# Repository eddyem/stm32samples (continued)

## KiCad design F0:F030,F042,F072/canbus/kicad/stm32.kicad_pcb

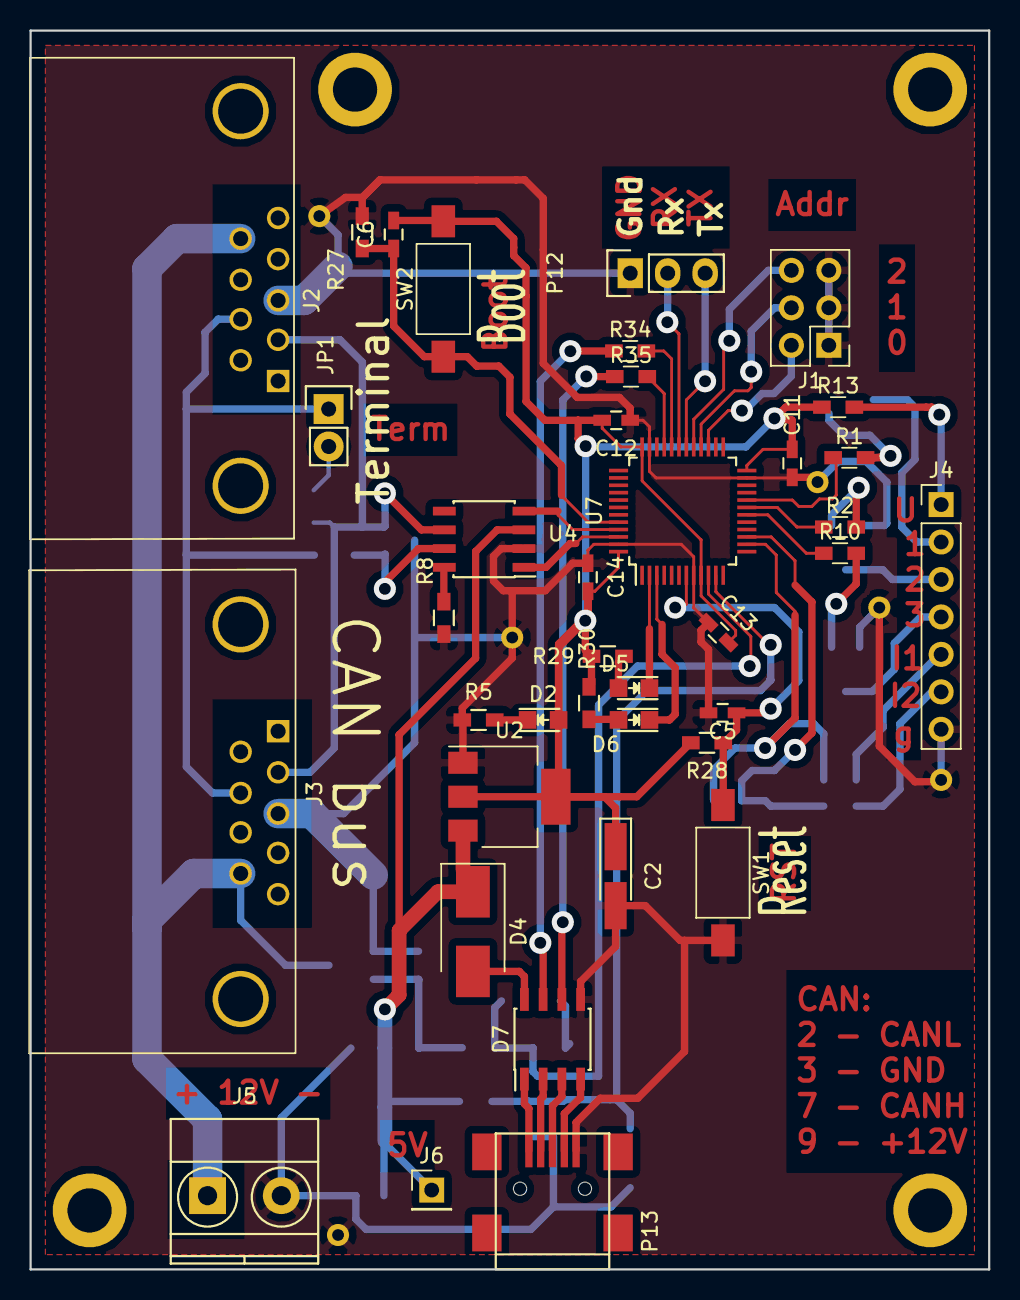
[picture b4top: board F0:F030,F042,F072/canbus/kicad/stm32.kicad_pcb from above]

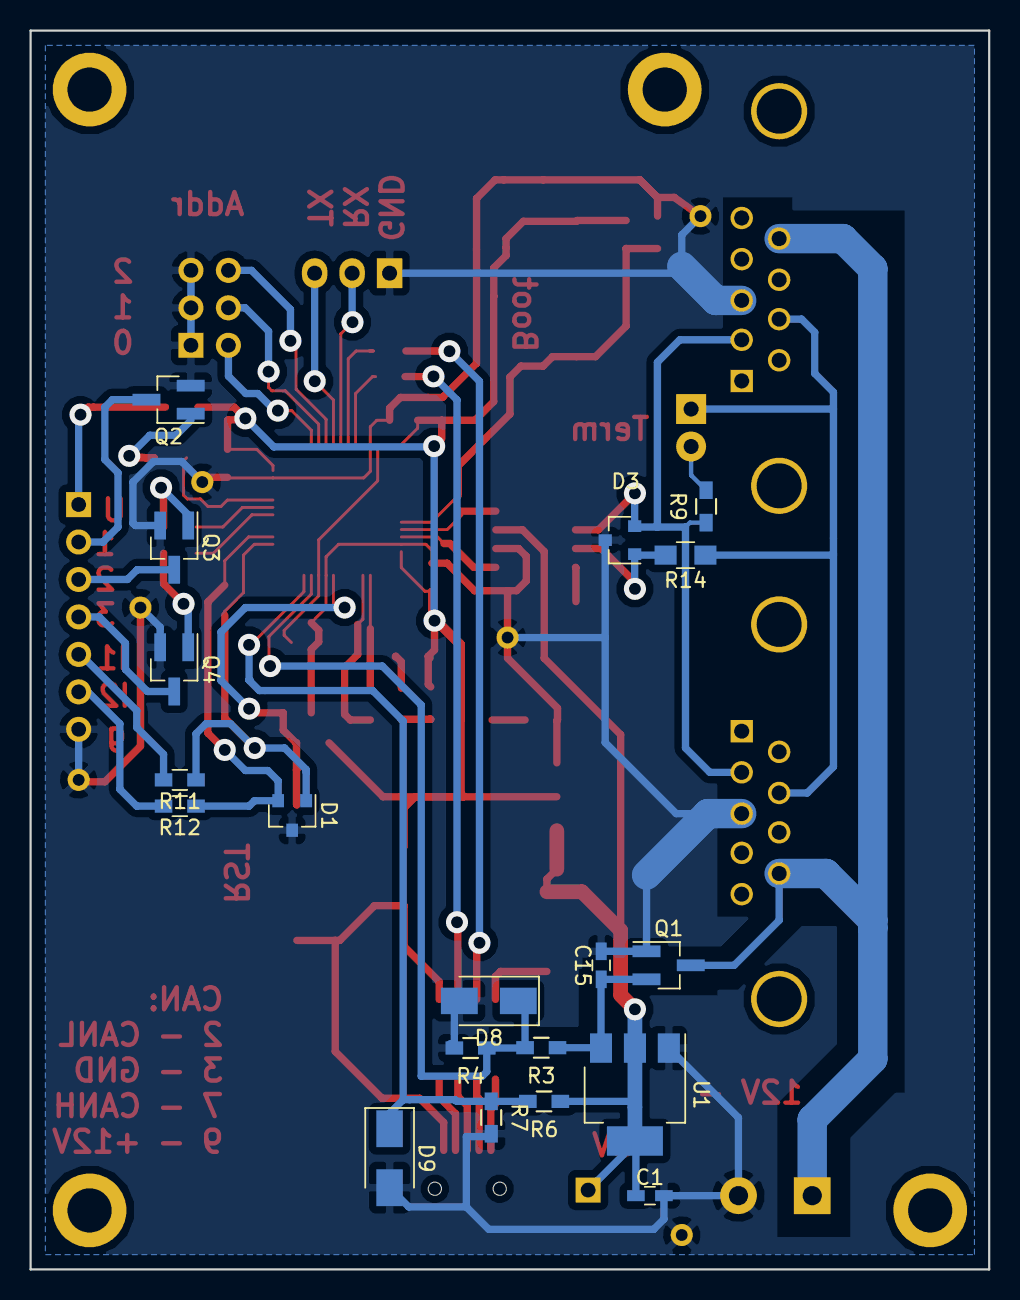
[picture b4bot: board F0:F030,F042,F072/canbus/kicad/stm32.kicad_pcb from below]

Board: 2 copper layers, 65.0 x 84.0 mm, 61 parts (19 on the bottom side), 49 nets.

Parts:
C1, C5, C6, C11, C12, C13, C14, C15: 0.1; C_0603_HandSoldering
C2: 47u; Tantalum_Case-A_EIA-3216-18_Hand
D1: SP0502BAHT; SOT-23
D2: LED; LED_0805
D3: PESD1CAN; SOT-23
D4: MBRS130L; D_SMB_Handsoldering
D5: LED0; LED_0805
D6: LED1; LED_0805
D7: USB6B1; SOIC-8_3.9x4.9mm_Pitch1.27mm
D8, D9: SMAJ5.0A; D_SMA
J1: CONN_02X03; Pin_Header_Straight_2x03_Pitch2.54mm
J2: DB9_Female; DB9FC
J3: DB9_Male; DB9MC
J4: Conn_01x07; Pin_Header_Straight_1x07_Pitch2.54mm
J5: 12v; TerminalBlock_Pheonix_MKDS1.5-2pol
J6: Conn_01x01; Pin_Header_Straight_1x01_Pitch2.54mm
JP1: Terminal; Pin_Header_Straight_1x02
P12: USART_BOOT; Pin_Header_Straight_1x03
P13: USB_A; USB_Mini-B
P15, P16, P17, P18: Hole; Hole_3mm
Q1: AO3407; SOT-23_Handsoldering
Q2, Q3, Q4: SI2300; SOT-23_Handsoldering
R1, R2, R5, R10, R11, R12, R29, R30: 330; R_0603_HandSoldering
R3: 220k; R_0603_HandSoldering
R4: 56k; R_0603_HandSoldering
R6, R7: 47k; R_0603_HandSoldering
R8: 4k7; R_0603_HandSoldering
R9: 120; R_0603_HandSoldering
R13: 4.7; R_0603_HandSoldering
R14: 0; R_0805_HandSoldering
R27, R28: 10k; R_0603_HandSoldering
R34, R35: 22; R_0603_HandSoldering
SW1: Reset; SW_SPST_FSMSM
SW2: Boot; SW_SPST_FSMSM
U1: LM1117-5.0; SOT-223
U2: LM1117-3.3; SOT-223
U4: MCP2551-I/SN; SOIC-8_3.9x4.9mm_Pitch1.27mm
U7: STM32F042C6Tx; LQFP-48_7x7mm_Pitch0.5mm

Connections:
+3V3: C2.1, C6.2, C11.2, C12.2, C13.2, C14.2, D2.2, R13.1, R28.2, R29.2, R30.2, SW2.2, U2.2, U2.4, U7.9, U7.24, U7.36, U7.48
+5V: C1.1, D4.1, J6.1, R6.1, U1.2, U1.4, U2.3, U4.3
/5Vusb: D4.2, D7.8
/12Vin: C15.1, Q1.2, R3.1, U1.3
/BOOT0: C6.1, R27.1, SW2.1, U7.44
/CAN_Rx: U4.4, U7.45
/CAN_Tx: U4.1, U7.46
/INP1: D1.1, R11.1, U7.14
/INP2: D1.2, R12.1, U7.15
/LED0: D5.1, U7.2
/LED1: D6.1, U7.3
/NRST: C5.1, R28.1, SW1.1, U7.7
/O1: R1.1, U7.20
/O2: R2.1, U7.19
/O3: R10.1, U7.18
/OUTP1: J4.2, Q2.3
/OUTP2: J4.3, Q3.3
/OUTP3: J4.4, Q4.3
/Rx: P12.2, U7.31
/Tx: P12.3, U7.30
/V5: D9.1, R6.2, R7.1, U7.11
/V12: D8.1, R3.2, R4.1, U7.10
/brdaddr0: J1.2, U7.27
/brdaddr1: J1.4, U7.28
/brdaddr2: J1.6, U7.29
GND: C1.2, C2.2, C5.2, C11.1, C12.1, C13.1, C14.1, C15.2, D1.3, D3.3, D7.5, D8.2, D9.2, J1.1, J1.3, J1.5, J2.3, J3.3, J4.7, J5.2, P12.1, P13.5, Q1.1, Q2.2, Q3.2, Q4.2, R4.2, R5.1, R7.2, R8.2, R27.2, SW1.2, U1.1, U2.1, U4.2, U7.8, U7.23, U7.35, U7.47
unnamed: D2.1, R5.2
unnamed: D3.1, R14.2, U4.7
unnamed: D3.2, J2.2, J3.2, R9.1, U4.6
unnamed: D5.2, R29.1
unnamed: D6.2, R30.1
unnamed: D7.1, P13.1
unnamed: D7.2, P13.2
unnamed: D7.3, P13.3
unnamed: D7.4, P13.4
unnamed: D7.6, R35.1
unnamed: D7.7, R34.1
unnamed: J2.7, J3.7, JP1.1, R14.1
unnamed: J2.9, J3.9, J5.1, Q1.3
unnamed: J4.1, R13.2
unnamed: J4.5, R11.2
unnamed: J4.6, R12.2
unnamed: JP1.2, R9.2
unnamed: Q2.1, R1.2
unnamed: Q3.1, R2.2
unnamed: Q4.1, R10.2
unnamed: R8.1, U4.8
unnamed: R34.2, U7.32
unnamed: R35.2, U7.33

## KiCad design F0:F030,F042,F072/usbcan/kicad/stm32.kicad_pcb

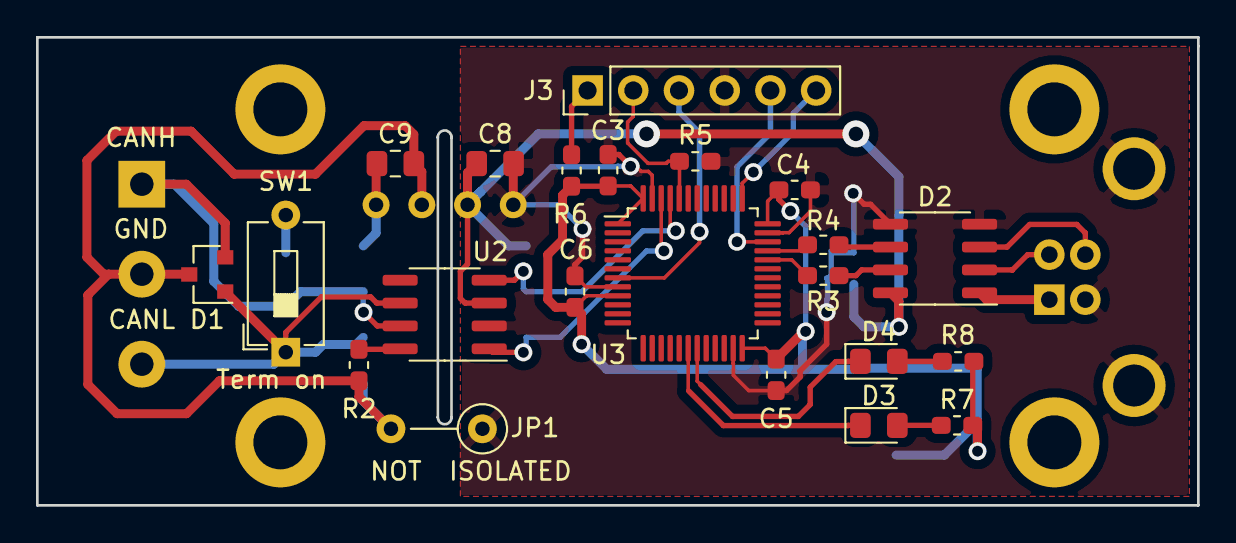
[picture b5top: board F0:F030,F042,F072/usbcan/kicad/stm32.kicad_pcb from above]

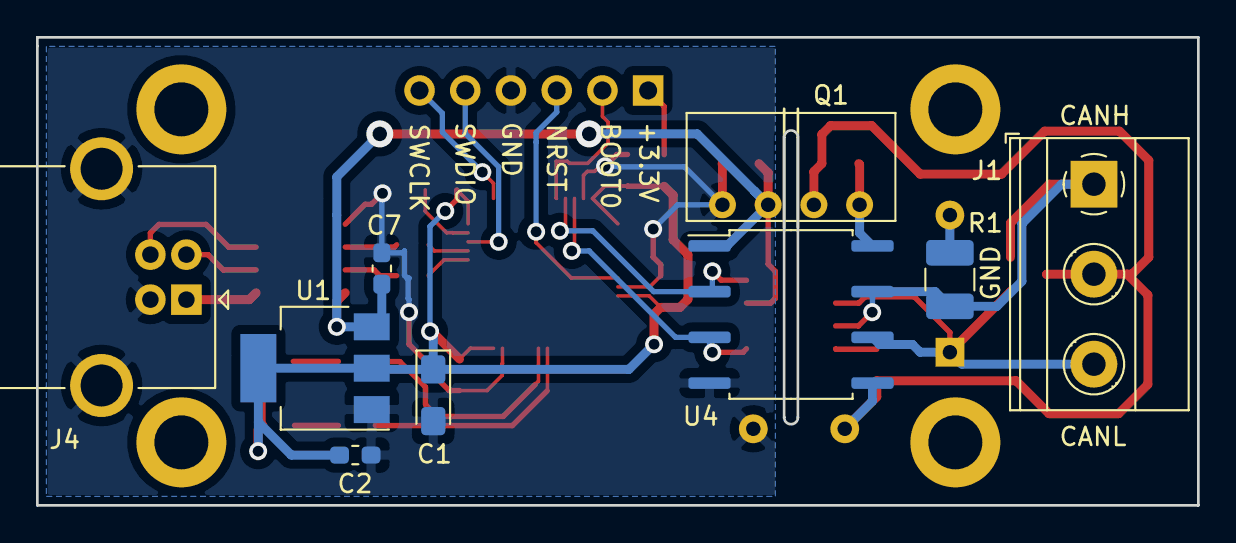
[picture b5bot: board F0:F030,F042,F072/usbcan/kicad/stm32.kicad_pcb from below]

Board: 2 copper layers, 64.5 x 26.0 mm, 35 parts (9 on the bottom side), 27 nets.

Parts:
C1: 47u; CP_EIA-3216-18_Kemet-A_Pad1.58x1.35mm_HandSolder
C2, C3, C4, C5, C6, C7: 0.1; C_0603_1608Metric_Pad1.05x0.95mm_HandSolder
C8, C9: 1; C_0805_2012Metric_Pad1.15x1.40mm_HandSolder
D1: PESD1CAN; SOT-23
D2: USB6B1; SOIC-8_3.9x4.9mm_P1.27mm
D3: LED0; LED_0805_2012Metric_Pad1.15x1.40mm_HandSolder
D4: LED1; LED_0805_2012Metric_Pad1.15x1.40mm_HandSolder
J1: Screw_Terminal_01x03; TerminalBlock_Phoenix_MKDS-1,5-3_1x03_P5.00mm_Horizontal
J3: SWDetc; PinHeader_1x06_P2.54mm_Vertical
J4: USB_B; USB_B_OST_USB-B1HSxx_Horizontal
JP1: NON-ISOL; R_Axial_DIN0207_L6.3mm_D2.5mm_P5.08mm_Vertical
P1, P2, P3, P4: Hole; Hole_3mm
Q1: B0505S; B0x0xS
R1: 120; R_1210_3225Metric_Pad1.42x2.65mm_HandSolder
R2: 4k7; R_0603_1608Metric_Pad1.05x0.95mm_HandSolder
R3, R4, R6: 22; R_0603_1608Metric_Pad1.05x0.95mm_HandSolder
R5: 10k; R_0603_1608Metric_Pad1.05x0.95mm_HandSolder
R7, R8: 330; R_0603_1608Metric_Pad1.05x0.95mm_HandSolder
SW1: SW_DIP_x01; SW_DIP_SPSTx01_Slide_6.7x4.1mm_W7.62mm_P2.54mm_LowProfile
U1: LM1117-3.3; SOT-223-3_TabPin2
U2: MCP2551-I/SN; SOIC-8_3.9x4.9mm_P1.27mm
U3: STM32F072C8Tx; LQFP-48_7x7mm_P0.5mm
U4: ISO1050DUB; SOP-8_6.62x9.15mm_P2.54mm

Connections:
+3V3: C1.1, C2.1, C3.2, C4.2, C5.2, C6.2, R6.1, R7.2, R8.2, U1.2, U3.1, U3.9, U3.24, U3.36, U3.48
+5V: C7.1, C8.1, D2.8, Q1.2, U1.3, U2.3, U4.1
/BOOT0: J3.2, R5.2, U3.44
/CANH: D1.2, J1.1, R1.2, U2.7, U4.7
/CANL: D1.1, J1.3, SW1.1, U2.6, U4.6
/CAN_Rx: U2.4, U3.45, U4.2
/CAN_Tx: U2.1, U3.46, U4.3
/LED0: D3.1, U3.18
/LED1: D4.1, U3.19
/NRST: J3.3, U3.7
/SWCLK: J3.6, U3.37
/SWDIO: J3.5, U3.34
Earth: C9.2, D1.3, J1.2, JP1.2, Q1.3, R2.2, U4.5
GND: C1.2, C2.2, C3.1, C4.1, C5.1, C6.1, C7.2, C8.2, D2.4, D2.5, J3.4, J4.4, J4.5, JP1.1, Q1.1, R5.1, U1.1, U2.2, U3.8, U3.23, U3.35, U3.47, U4.4
unnamed: C9.1, Q1.4, U4.8
unnamed: D2.1, J4.1
unnamed: D2.2, J4.2
unnamed: D2.3, J4.3
unnamed: D2.6, R4.1
unnamed: D2.7, R3.1
unnamed: D3.2, R7.1
unnamed: D4.2, R8.1
unnamed: J3.1, R6.2
unnamed: R1.1, SW1.2
unnamed: R2.1, U2.8
unnamed: R3.2, U3.32
unnamed: R4.2, U3.33

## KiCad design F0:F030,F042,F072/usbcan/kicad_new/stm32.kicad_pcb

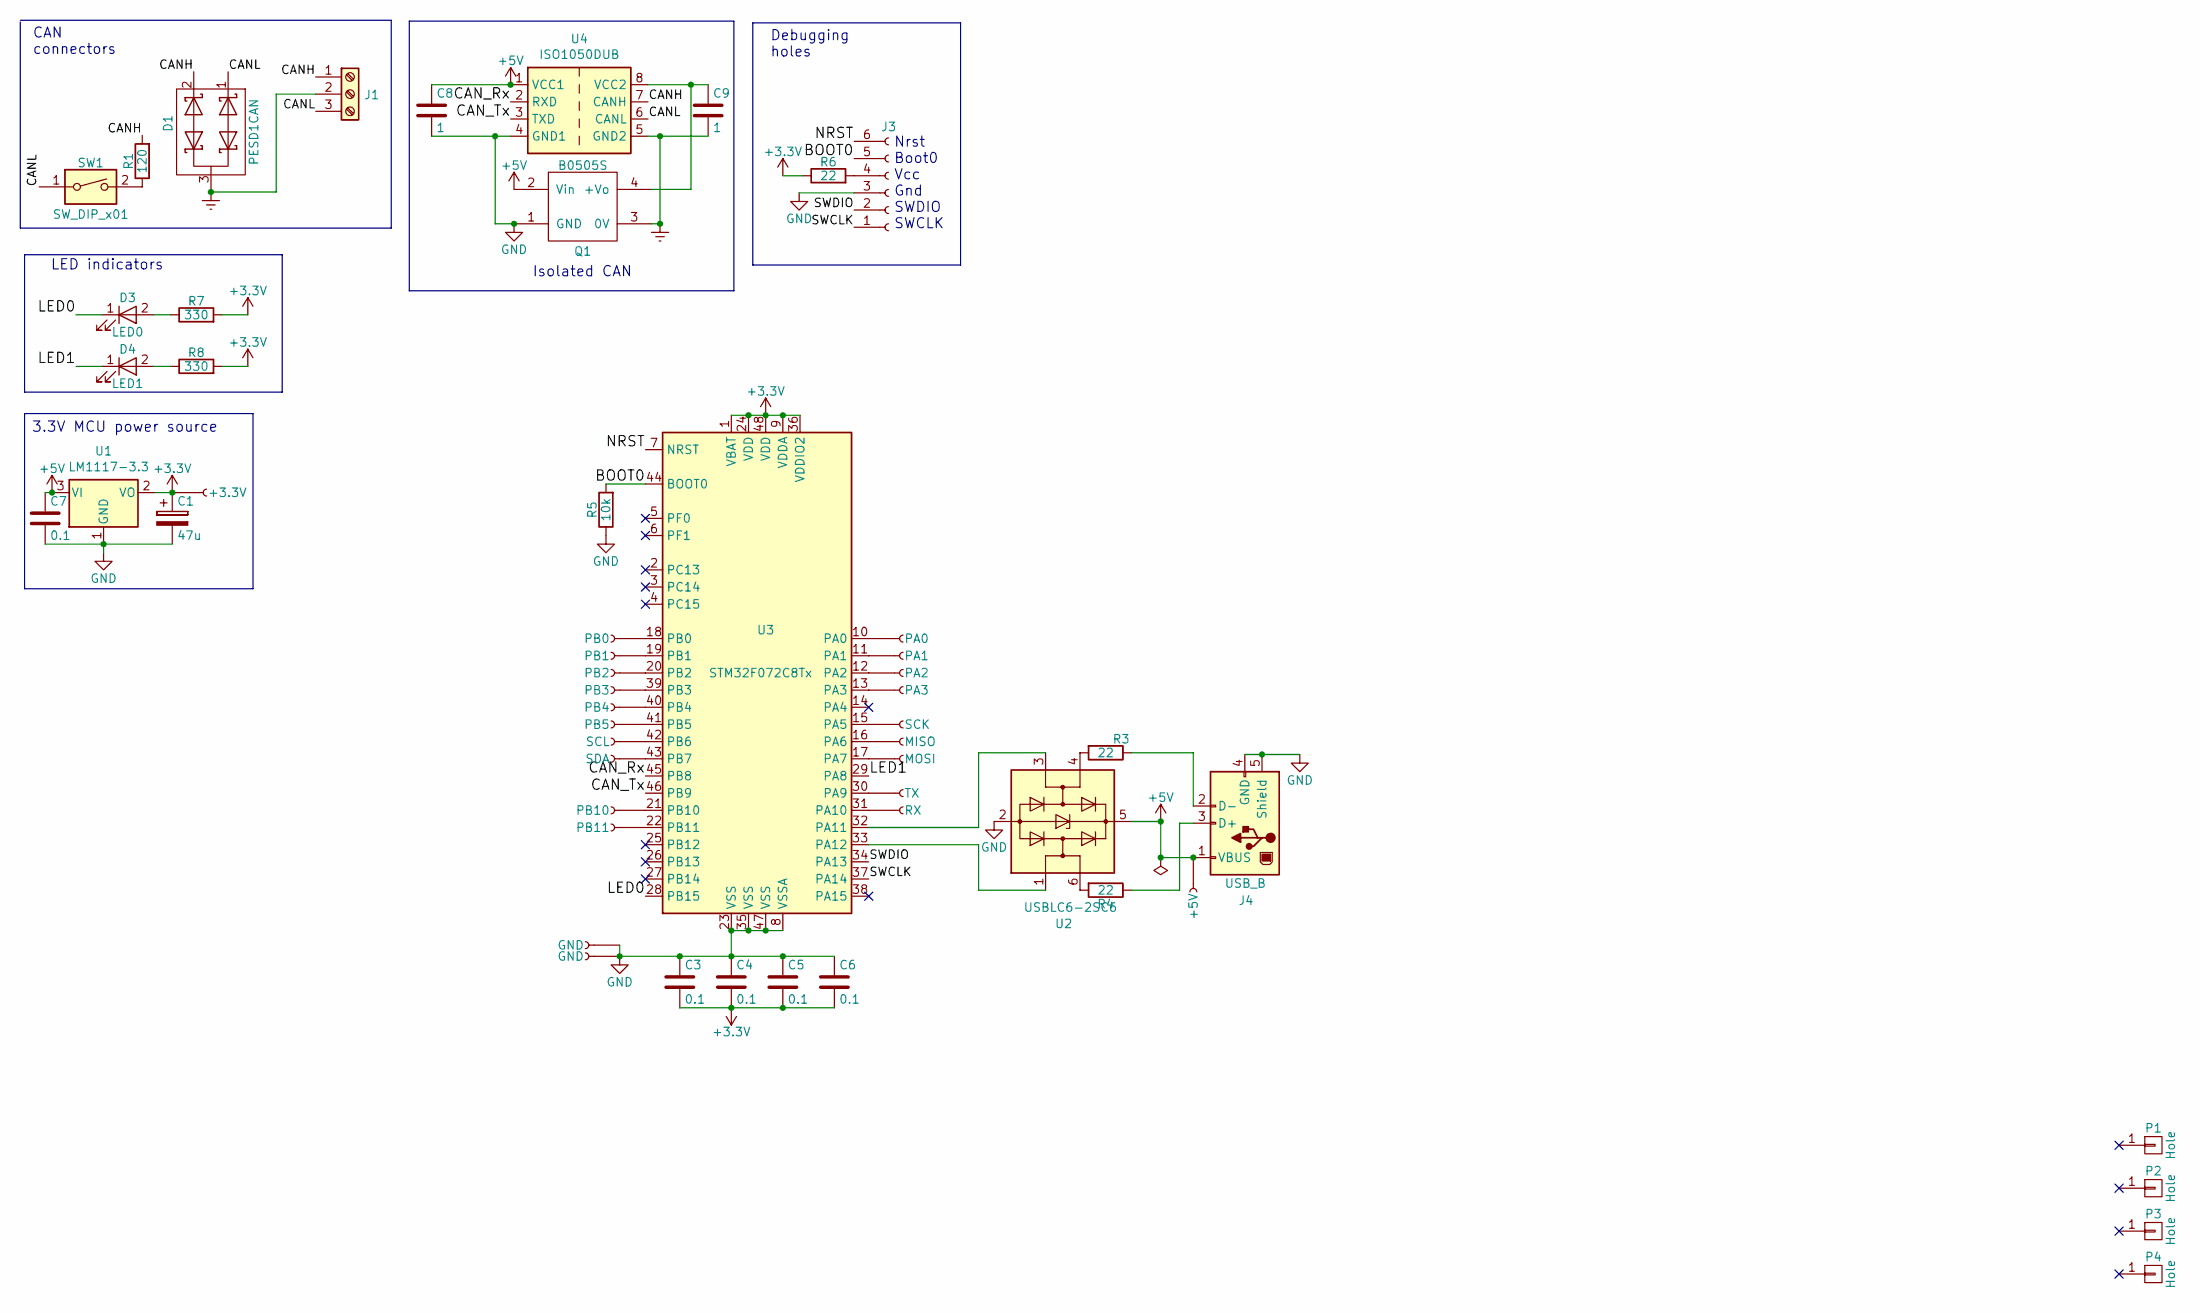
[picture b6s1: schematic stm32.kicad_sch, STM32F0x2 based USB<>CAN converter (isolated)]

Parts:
C1: 47u; CP_EIA-3216-18_Kemet-A_Pad1.58x1.35mm_HandSolder
C3, C4, C5, C6, C7: 0.1; C_0603_1608Metric_Pad1.05x0.95mm_HandSolder
C8, C9: 1; C_0805_2012Metric_Pad1.15x1.40mm_HandSolder
D1: PESD1CAN; SOT-23
D3: LED0; LED_0805_2012Metric_Pad1.15x1.40mm_HandSolder
D4: LED1; LED_0805_2012Metric_Pad1.15x1.40mm_HandSolder
J1: Screw_Terminal_01x03; TerminalBlock_Phoenix_MKDS-1,5-3_1x03_P5.00mm_Horizontal
J2: SCK; TestPoint_THTPad_1.5x1.5mm_Drill0.7mm
J3: SWDetc; PinHeader_1x06_P1.27mm_Vertical
J4: USB_B; USB_B_Lumberg_2411_02_Horizontal
J5: MISO; TestPoint_THTPad_1.5x1.5mm_Drill0.7mm
J6: MOSI; TestPoint_THTPad_1.5x1.5mm_Drill0.7mm
J7: TX; TestPoint_THTPad_1.5x1.5mm_Drill0.7mm
J8: RX; TestPoint_THTPad_1.5x1.5mm_Drill0.7mm
J9: SCL; TestPoint_THTPad_1.5x1.5mm_Drill0.7mm
J10: SDA; TestPoint_THTPad_1.5x1.5mm_Drill0.7mm
J11: PB0; TestPoint_THTPad_1.5x1.5mm_Drill0.7mm
J12: PB1; TestPoint_THTPad_1.5x1.5mm_Drill0.7mm
J13: PB4; TestPoint_THTPad_1.5x1.5mm_Drill0.7mm
J14: PB5; TestPoint_THTPad_1.5x1.5mm_Drill0.7mm
J15: PB2; TestPoint_THTPad_1.5x1.5mm_Drill0.7mm
J16: PB3; TestPoint_THTPad_1.5x1.5mm_Drill0.7mm
J17, J18: GND; TestPoint_THTPad_1.5x1.5mm_Drill0.7mm
J19: +3.3V; TestPoint_THTPad_1.5x1.5mm_Drill0.7mm
J20: +5V; TestPoint_THTPad_1.5x1.5mm_Drill0.7mm
J21: PA0; TestPoint_THTPad_1.0x1.0mm_Drill0.5mm
J22: PA1; TestPoint_THTPad_1.0x1.0mm_Drill0.5mm
J23: PA2; TestPoint_THTPad_1.0x1.0mm_Drill0.5mm
J24: PA3; TestPoint_THTPad_1.0x1.0mm_Drill0.5mm
J25: PB10; TestPoint_THTPad_1.5x1.5mm_Drill0.7mm
J26: PB11; TestPoint_THTPad_1.5x1.5mm_Drill0.7mm
P1, P2, P3, P4: Hole; Hole_3mm
Q1: B0505S; B0x0xS
R1: 120; R_1210_3225Metric_Pad1.42x2.65mm_HandSolder
R3, R4, R6: 22; R_0603_1608Metric_Pad1.05x0.95mm_HandSolder
R5: 10k; R_0603_1608Metric_Pad1.05x0.95mm_HandSolder
R7, R8: 330; R_0603_1608Metric_Pad1.05x0.95mm_HandSolder
SW1: SW_DIP_x01; SW_DIP_SPSTx01_Slide_6.7x4.1mm_W7.62mm_P2.54mm_LowProfile
U1: LM1117-3.3; SOT-223-3_TabPin2
U2: USBLC6-2SC6; SOT-23-6_Handsoldering
U3: STM32F072C8Tx; LQFP-48_7x7mm_P0.5mm
U4: ISO1050DUB; SOP-8_6.62x9.15mm_P2.54mm

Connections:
+3V3: C1.1, C3.2, C4.2, C5.2, C6.2, J19.1, R6.1, R7.2, R8.2, U1.2 (VO), U3.1 (VBAT), U3.9 (VDDA), U3.24 (VDD), U3.36 (VDDIO2), U3.48 (VDD)
+5V: C7.1, C8.1, J4.1 (VBUS), J20.1, Q1.2 (Vin), U1.3 (VI), U2.5 (VBUS), U4.1 (VCC1)
/BOOT0: J3.5, R5.2, U3.44 (BOOT0)
/CANH: D1.2 (K), J1.1, R1.2, U4.7 (CANH)
/CANL: D1.1 (K), J1.3, SW1.1, U4.6 (CANL)
/CAN_Rx: U3.45 (PB8), U4.2 (RXD)
/CAN_Tx: U3.46 (PB9), U4.3 (TXD)
/LED0: D3.1 (K), U3.28 (PB15)
/LED1: D4.1 (K), U3.29 (PA8)
/NRST: J3.6, U3.7 (NRST)
/SWCLK: J3.1, U3.37 (PA14)
/SWDIO: J3.2, U3.34 (PA13)
Earth: C9.2, D1.3 (O), J1.2, Q1.3 (0V), U4.5 (GND2)
GND: C1.2, C3.1, C4.1, C5.1, C6.1, C7.2, C8.2, J3.3, J4.4 (GND), J4.5 (Shield), J17.1, J18.1, Q1.1 (GND), R5.1, U1.1 (GND), U2.2 (GND), U3.8 (VSSA), U3.23 (VSS), U3.35 (VSS), U3.47 (VSS), U4.4 (GND1)
unnamed: C9.1, Q1.4 (+Vo), U4.8 (VCC2)
unnamed: D3.2 (A), R7.1
unnamed: D4.2 (A), R8.1
unnamed: J2.1, U3.15 (PA5)
unnamed: J3.4, R6.2
unnamed: J4.2 (D-), R3.1
unnamed: J4.3 (D+), R4.1
unnamed: J5.1, U3.16 (PA6)
unnamed: J6.1, U3.17 (PA7)
unnamed: J7.1, U3.30 (PA9)
unnamed: J8.1, U3.31 (PA10)
unnamed: J9.1, U3.42 (PB6)
unnamed: J10.1, U3.43 (PB7)
unnamed: J11.1, U3.18 (PB0)
unnamed: J12.1, U3.19 (PB1)
unnamed: J13.1, U3.40 (PB4)
unnamed: J14.1, U3.41 (PB5)
unnamed: J15.1, U3.20 (PB2)
unnamed: J16.1, U3.39 (PB3)
unnamed: J21.1, U3.10 (PA0)
unnamed: J22.1, U3.11 (PA1)
unnamed: J23.1, U3.12 (PA2)
unnamed: J24.1, U3.13 (PA3)
unnamed: J25.1, U3.21 (PB10)
unnamed: J26.1, U3.22 (PB11)
unnamed: R1.1, SW1.2
unnamed: R3.2, U2.4 (I/O2)
unnamed: R4.2, U2.6 (I/O1)
unnamed: U2.1 (I/O1), U3.33 (PA12)
unnamed: U2.3 (I/O2), U3.32 (PA11)

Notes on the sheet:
LED indicators
Isolated CAN
Debugging holes
3.3V MCU power source
Nrst Boot0 Vcc Gnd SWDIO SWCLK
CAN connectors

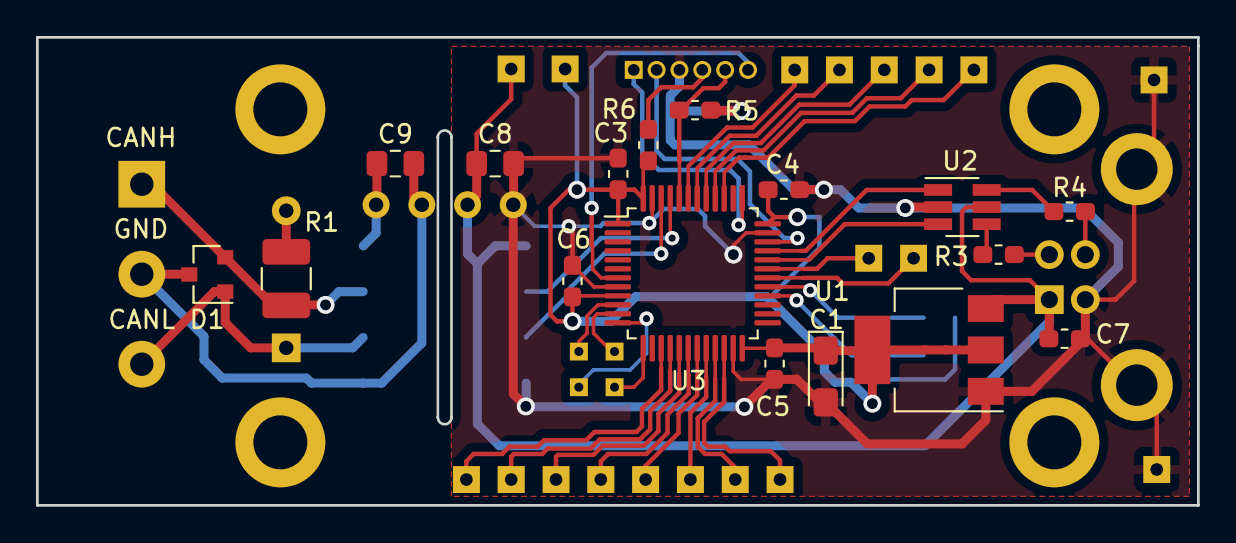
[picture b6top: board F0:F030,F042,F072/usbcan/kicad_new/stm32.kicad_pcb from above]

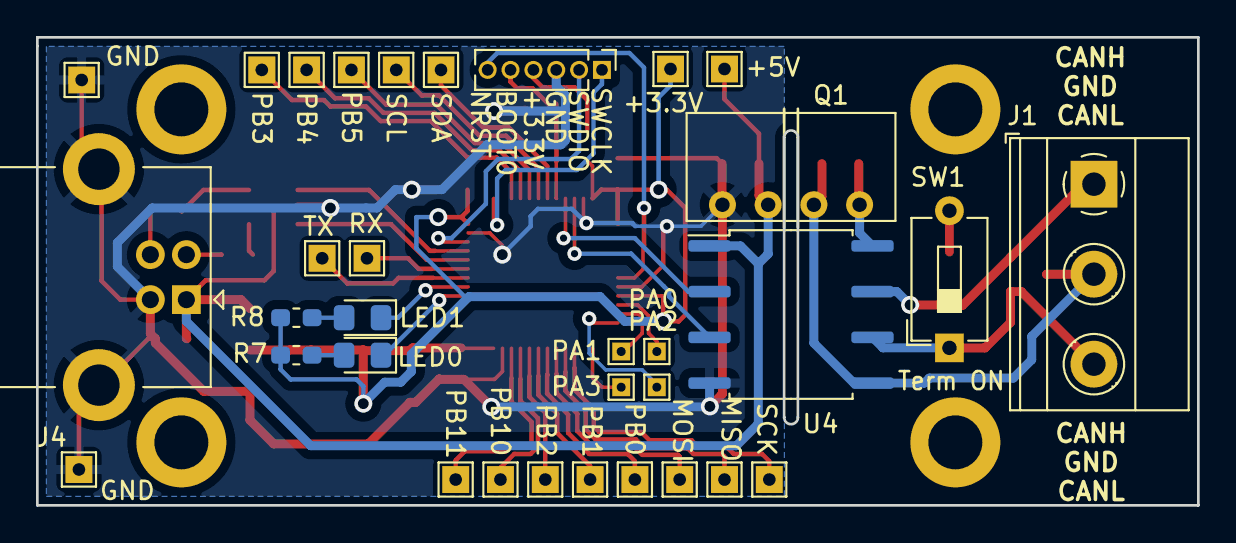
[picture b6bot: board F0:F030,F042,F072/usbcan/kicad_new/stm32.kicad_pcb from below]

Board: 2 copper layers, 64.5 x 26.0 mm, 54 parts (33 on the bottom side), 44 nets.

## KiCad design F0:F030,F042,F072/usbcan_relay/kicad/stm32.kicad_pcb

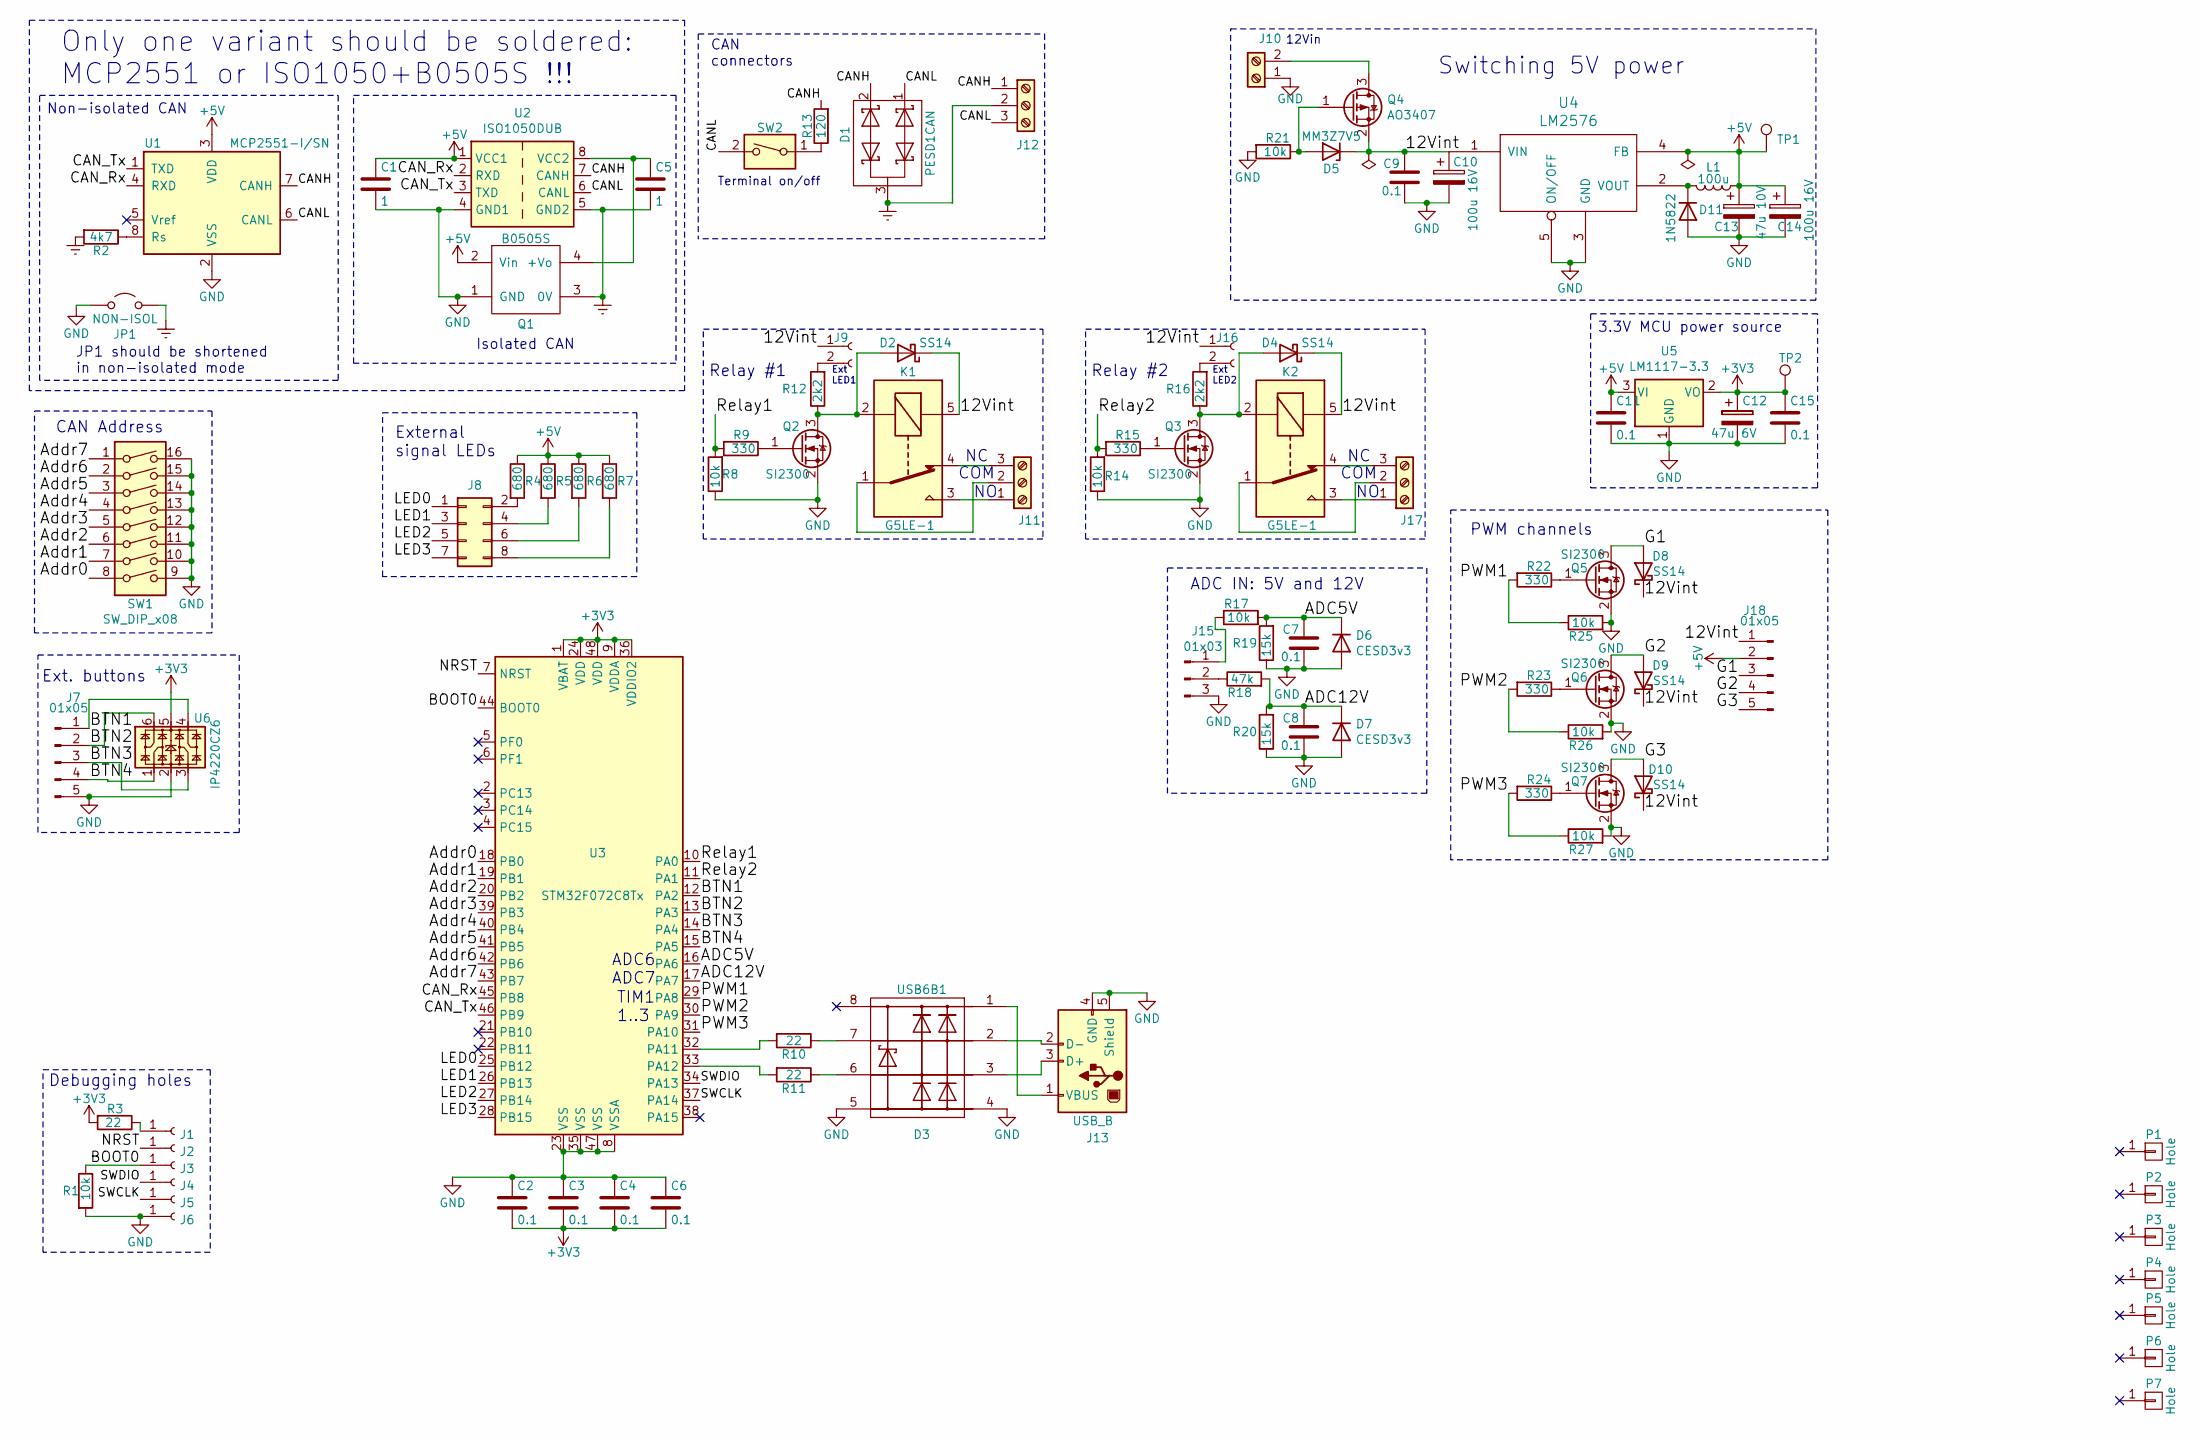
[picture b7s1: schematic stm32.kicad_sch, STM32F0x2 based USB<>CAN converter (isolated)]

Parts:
C1, C5: 1; C_0805_2012Metric_Pad1.15x1.40mm_HandSolder
C2, C3, C4, C6, C7, C8, C9, C11, C15: 0.1; C_0603_1608Metric_Pad1.05x0.95mm_HandSolder
C10, C14: 100u 16V; CP_Radial_D8.0mm_P3.50mm
C12: 47u 6V; CP_EIA-3216-18_Kemet-A_Pad1.58x1.35mm_HandSolder
C13: 47u 10V; CP_EIA-6032-28_Kemet-C_Pad2.25x2.35mm_HandSolder
D1: PESD1CAN; SOT-23
D2, D4, D8, D9, D10: SS14; D_SMA-SMB_Universal_Handsoldering
D3: USB6B1; SOIC-8_3.9x4.9mm_P1.27mm
D5: MM3Z7V5; D_0805_2012Metric_Pad1.15x1.40mm_HandSolder
D6, D7: CESD3v3; D_SOD-523
D11: 1N5822; D_DO-201_P3.81mm_Vertical_AnodeUp
J1: +3.3V; PinHeader_1x01_P2.54mm_Vertical
J2: NRST; PinHeader_1x01_P2.54mm_Vertical
J3: BOOT0; PinHeader_1x01_P2.54mm_Vertical
J4: SWDIO; PinHeader_1x01_P2.54mm_Vertical
J5: SWCLK; PinHeader_1x01_P2.54mm_Vertical
J6: GND; PinHeader_1x01_P2.54mm_Vertical
J7: 01x05; PinHeader_1x05_P2.54mm_Vertical
J8: Connector_Generic:Conn_02x04_Odd_Even; PinHeader_2x04_P2.54mm_Vertical
J9, J16: Conn_01x02_Female; PinSocket_1x02_P2.54mm_Vertical
J10: Screw_Terminal_01x02; TerminalBlock_Phoenix_MKDS-1,5-2_1x02_P5.00mm_Horizontal
J11, J12, J17: Screw_Terminal_01x03; TerminalBlock_Phoenix_MKDS-1,5-3_1x03_P5.00mm_Horizontal
J13: USB_B; USB_B_OST_USB-B1HSxx_Horizontal
J15: 01x03; PinSocket_1x03_P2.54mm_Vertical
J18: 01x05; PinSocket_1x05_P2.54mm_Vertical
JP1: NON-ISOL; R_Axial_DIN0207_L6.3mm_D2.5mm_P5.08mm_Vertical
K1, K2: G5LE-1; Relay_SPDT_SANYOU_SRD_Series_Form_C
L1: 100u; L_12x12mm_H4.5mm
P1, P2, P3, P4, P5, P6, P7: Hole; Hole_3mm
Q1: B0505S; B0x0xS
Q2, Q3, Q5, Q6, Q7: SI2300; SOT-23_Handsoldering
Q4: AO3407; SOT-23_Handsoldering
R1, R8, R14, R17, R21, R25, R26, R27: 10k; R_0603_1608Metric_Pad1.05x0.95mm_HandSolder
R2: 4k7; R_0603_1608Metric_Pad1.05x0.95mm_HandSolder
R3, R10, R11: 22; R_0603_1608Metric_Pad1.05x0.95mm_HandSolder
R4, R5, R6, R7: 680; R_0603_1608Metric_Pad1.05x0.95mm_HandSolder
R9, R15, R22, R23, R24: 330; R_0603_1608Metric_Pad1.05x0.95mm_HandSolder
R12, R16: 2k2; R_0603_1608Metric_Pad1.05x0.95mm_HandSolder
R13: 120; R_1210_3225Metric_Pad1.42x2.65mm_HandSolder
R18: 47k; R_0603_1608Metric_Pad1.05x0.95mm_HandSolder
R19, R20: 15k; R_0603_1608Metric_Pad1.05x0.95mm_HandSolder
SW1: SW_DIP_x08; SW_DIP_SPSTx08_Slide_9.78x22.5mm_W7.62mm_P2.54mm
SW2: SW_DIP_x01; SW_DIP_SPSTx01_Slide_6.7x4.1mm_W7.62mm_P2.54mm_LowProfile
TP1: 5V; PinSocket_1x01_P2.54mm_Vertical
TP2: 3.3V; PinSocket_1x01_P2.54mm_Vertical
U1: MCP2551-I/SN; SOIC-8_3.9x4.9mm_P1.27mm
U2: ISO1050DUB; SOP-8_6.62x9.15mm_P2.54mm
U3: STM32F072C8Tx; LQFP-48_7x7mm_P0.5mm
U4: LM2576; TO-220-5_P3.4x3.7mm_StaggerEven_Lead3.8mm_Vertical
U5: LM1117-3.3; SOT-223-3_TabPin2
U6: IP4220CZ6; TSOP-6_1.65x3.05mm_P0.95mm

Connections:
+3V3: C2.2, C3.2, C4.2, C6.2, C12.1, C15.1, R3.2, TP2.1, U3.1 (VBAT), U3.9 (VDDA), U3.24 (VDD), U3.36 (VDDIO2), U3.48 (VDD), U5.2 (VO), U6.5
+5V: C1.1, C11.1, C13.1, C14.1, J18.2, L1.1, Q1.2 (Vin), R4.1, R5.1, R6.1, R7.1, TP1.1, U1.3 (VDD), U2.1 (VCC1), U4.4 (FB), U5.3 (VI)
/12Vint: C9.1, C10.1, D2.1 (K), D4.1 (K), D5.1 (K), D8.1 (K), D9.1 (K), D10.1 (K), J9.1, J16.1, J18.1, K1.5, K2.5, Q4.2 (S), U4.1 (VIN)
/ADC5V: C7.1, D6.1 (K), R17.2, R19.2, U3.16 (PA6)
/ADC12V: C8.1, D7.1 (K), R18.2, R20.2, U3.17 (PA7)
/Addr0: SW1.8, U3.18 (PB0)
/Addr1: SW1.7, U3.19 (PB1)
/Addr2: SW1.6, U3.20 (PB2)
/Addr3: SW1.5, U3.39 (PB3)
/Addr4: SW1.4, U3.40 (PB4)
/Addr5: SW1.3, U3.41 (PB5)
/Addr6: SW1.2, U3.42 (PB6)
/Addr7: SW1.1, U3.43 (PB7)
/BOOT0: J3.1, R1.1, U3.44 (BOOT0)
/BTN1: J7.1, U3.12 (PA2), U6.4
/BTN2: J7.2, U3.13 (PA3), U6.6
/BTN3: J7.3, U3.14 (PA4), U6.3
/BTN4: J7.4, U3.15 (PA5), U6.1
/CANH: D1.2 (K), J12.1, R13.2, U1.7 (CANH), U2.7 (CANH)
/CANL: D1.1 (K), J12.3, SW2.2, U1.6 (CANL), U2.6 (CANL)
/CAN_Rx: U1.4 (RXD), U2.2 (RXD), U3.45 (PB8)
/CAN_Tx: U1.1 (TXD), U2.3 (TXD), U3.46 (PB9)
/G1: D8.2 (A), J18.3, Q5.3 (D)
/G2: D9.2 (A), J18.4, Q6.3 (D)
/G3: D10.2 (A), J18.5, Q7.3 (D)
/LED0: J8.1, U3.25 (PB12)
/LED1: J8.3, U3.26 (PB13)
/LED2: J8.5, U3.27 (PB14)
/LED3: J8.7, U3.28 (PB15)
/NRST: J2.1, U3.7 (NRST)
/PWM1: R22.2, R25.1, U3.29 (PA8)
/PWM2: R23.2, R26.1, U3.30 (PA9)
/PWM3: R24.2, R27.1, U3.31 (PA10)
/Relay1: R8.2, R9.2, U3.10 (PA0)
/Relay2: R14.2, R15.2, U3.11 (PA1)
/SWCLK: J5.1, U3.37 (PA14)
/SWDIO: J4.1, U3.34 (PA13)
Earth: C5.2, D1.3 (O), J12.2, JP1.2 (B), Q1.3 (0V), R2.2, U2.5 (GND2)
GND: C1.2, C2.1, C3.1, C4.1, C6.1, C7.2, C8.2, C9.2, C10.2, C11.2, C12.2, C13.2, C14.2, C15.2, D3.4 (GND), D3.5 (GND), D6.2 (A), D7.2 (A), D11.2 (A), J6.1, J7.5, J10.1, J13.4 (GND), J13.5 (Shield), J15.3, JP1.1 (A), Q1.1 (GND), Q2.2 (S), Q3.2 (S), Q5.2 (S), Q6.2 (S), Q7.2 (S), R1.2, R8.1, R14.1, R19.1, R20.1, R21.2, R25.2, R26.2, R27.2, SW1.9, SW1.10, SW1.11, SW1.12, SW1.13, SW1.14, SW1.15, SW1.16, U1.2 (VSS), U2.4 (GND1), U3.8 (VSSA), U3.23 (VSS), U3.35 (VSS), U3.47 (VSS), U4.3 (GND), U4.5 (ON/OFF), U5.1 (GND), U6.2
unnamed: C5.1, Q1.4 (+Vo), U2.8 (VCC2)
unnamed: D2.2 (A), K1.2, Q2.3 (D), R12.1
unnamed: D3.1 (VCC), J13.1 (VBUS)
unnamed: D3.2 (I/O1), J13.2 (D-)
unnamed: D3.3 (I/O2), J13.3 (D+)
unnamed: D3.6 (I/O2), R11.1
unnamed: D3.7 (I/O1), R10.1
unnamed: D4.2 (A), K2.2, Q3.3 (D), R16.1
unnamed: D5.2 (A), Q4.1 (G), R21.1
unnamed: D11.1 (K), L1.2, U4.2 (VOUT)
unnamed: J1.1, R3.1
unnamed: J8.2, R4.2
unnamed: J8.4, R5.2
unnamed: J8.6, R6.2
unnamed: J8.8, R7.2
unnamed: J9.2, R12.2
unnamed: J10.2, Q4.3 (D)
unnamed: J11.1, K1.3
unnamed: J11.2, K1.1
unnamed: J11.3, K1.4
unnamed: J15.1, R17.1
unnamed: J15.2, R18.1
unnamed: J16.2, R16.2
unnamed: J17.1, K2.3
unnamed: J17.2, K2.1
unnamed: J17.3, K2.4
unnamed: Q2.1 (G), R9.1
unnamed: Q3.1 (G), R15.1
unnamed: Q5.1 (G), R22.1
unnamed: Q6.1 (G), R23.1
unnamed: Q7.1 (G), R24.1
unnamed: R2.1, U1.8 (Rs)
unnamed: R10.2, U3.32 (PA11)
unnamed: R11.2, U3.33 (PA12)
unnamed: R13.1, SW2.1

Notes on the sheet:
3.3V MCU power source
Ext LED2
Relay #1
Ext LED1
Isolated CAN
ADC6 ADC7
External signal LEDs
CAN connectors
Ext. buttons
TIM1 1..3
CAN Address
Relay #2
Non-isolated CAN
Debugging holes
COM
ADC IN: 5V and 12V
Only one variant should be soldered: MCP2551 or ISO1050+B0505S !!!
PWM channels
JP1 should be shortened in non-isolated mode
Switching 5V power
12Vin
Terminal on/off

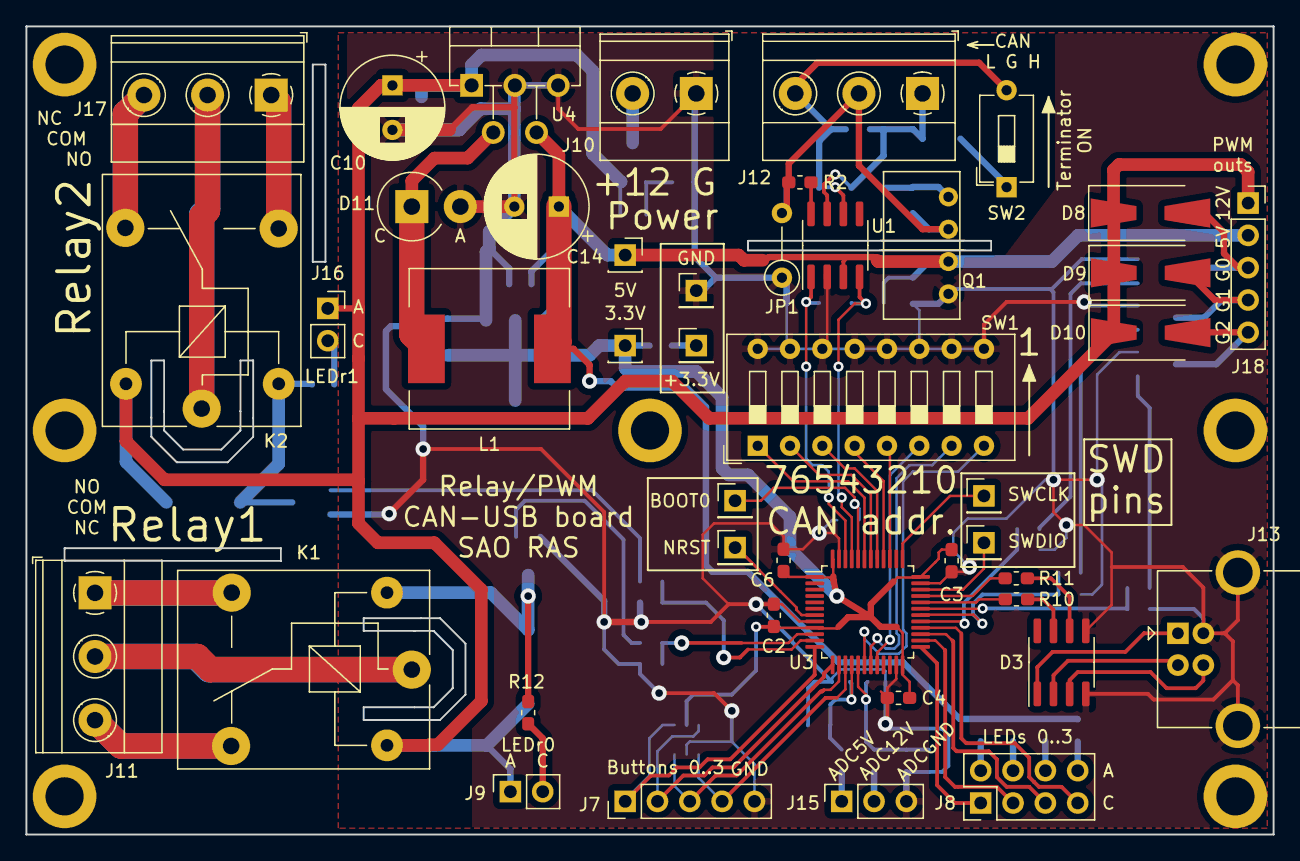
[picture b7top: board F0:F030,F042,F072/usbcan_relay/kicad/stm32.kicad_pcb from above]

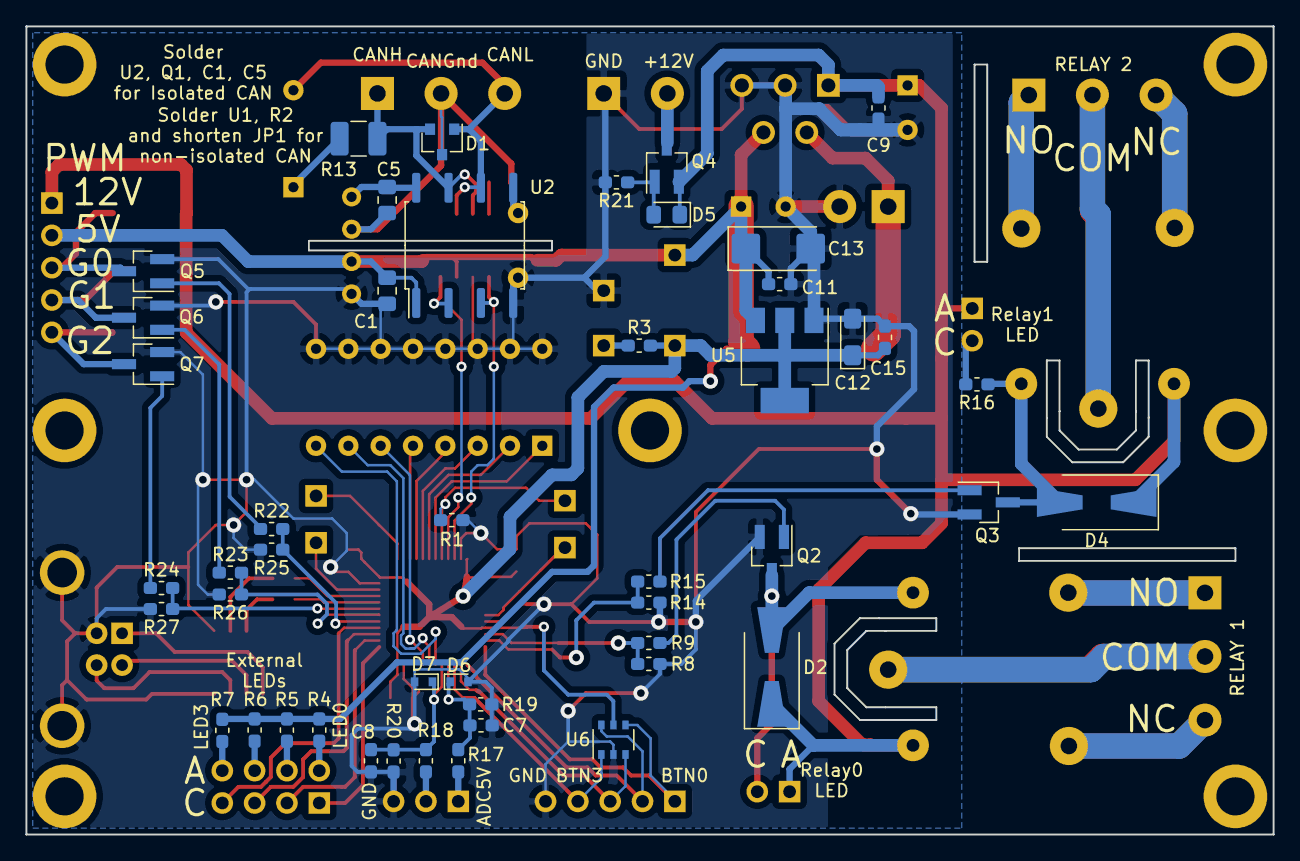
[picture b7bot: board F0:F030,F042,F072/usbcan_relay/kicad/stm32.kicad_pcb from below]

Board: 2 copper layers, 98.0 x 63.5 mm, 98 parts (47 on the bottom side), 74 nets.
